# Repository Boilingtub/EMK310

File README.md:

#========== Implemented Mappings Final ===========
RA0 - SSD-0
RA1 - SSD-1
RA2 - SSD-2
RA3 - SSD-3
RA4 - SSD-4
RA5 - SSD-5
RA6 - SSD-6
RA7 - 

RB0 - USB-to-UART RST
RB1 - 
RB2 - 
RB3 - MOTOR_2_B
RB4 - 
RB5 - Capacitive Touch Sensor
RB6 -  
RB7 - LEDB

RC0 - LEDR
RC1 - LEDG
RC2 - (CCP1) MOTOR_1_B 
RC3 - SCL 1
RC4 - SDA 1
RC5 - Sensor 2
RC6 - Sensor 1
RC7 - Sensor 0

RD0 - SCL2
RD1 - SDA2
RD2 - Sensor 5
RD3 - Sensor 4
RD4 - 
RD5 - 
RD6 - TX
RD7 - RX

RE0 - MOTOR_2_F 
RE1 - 
RE2 - MOTOR_1_F
RE3 - PROGRAMMING PIN

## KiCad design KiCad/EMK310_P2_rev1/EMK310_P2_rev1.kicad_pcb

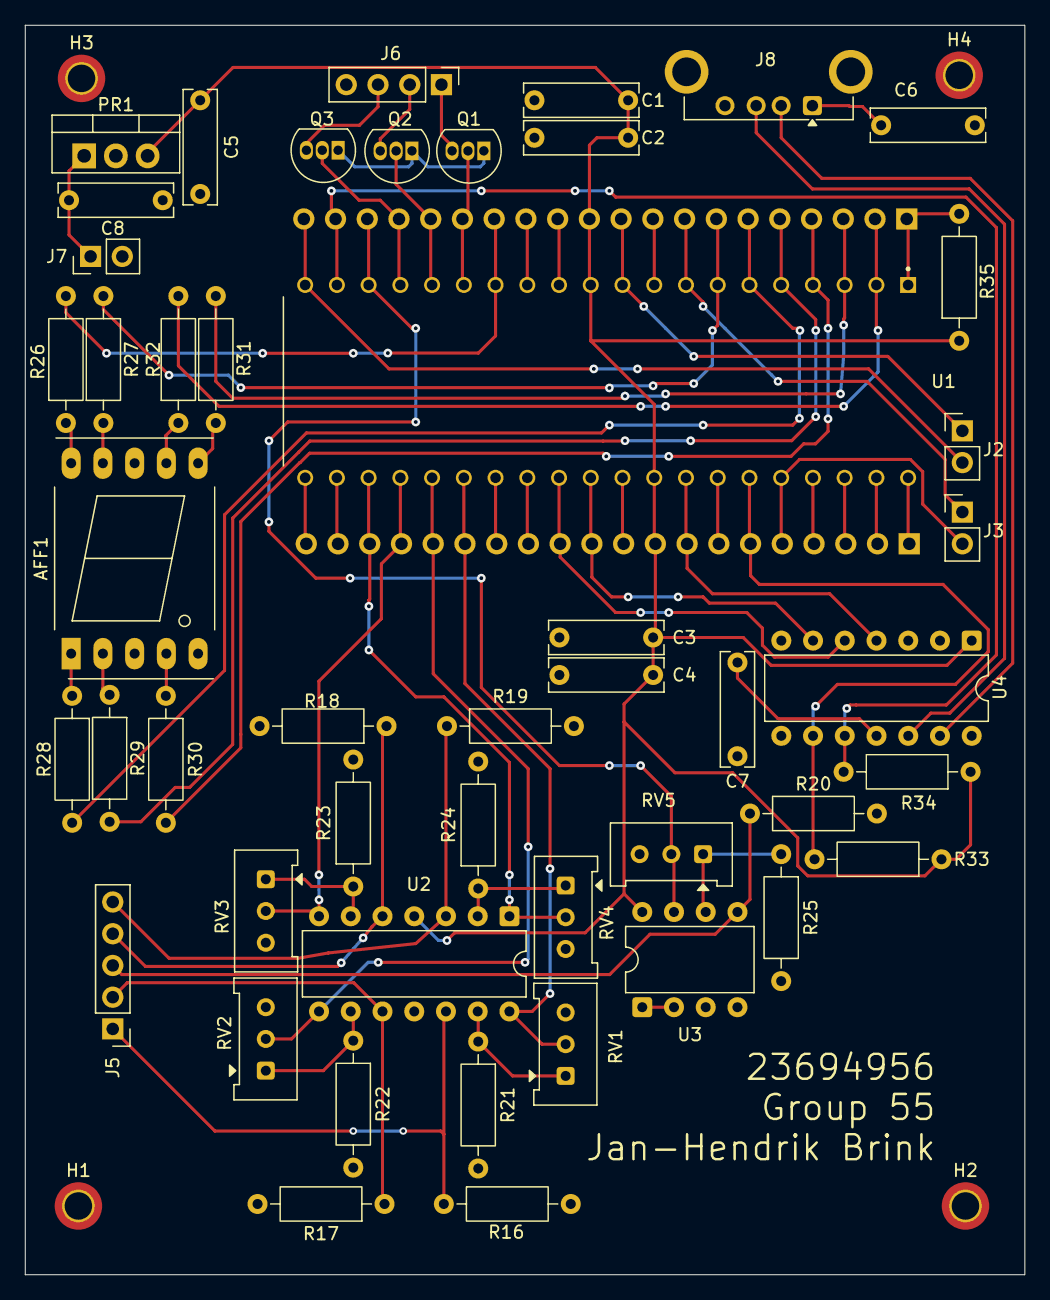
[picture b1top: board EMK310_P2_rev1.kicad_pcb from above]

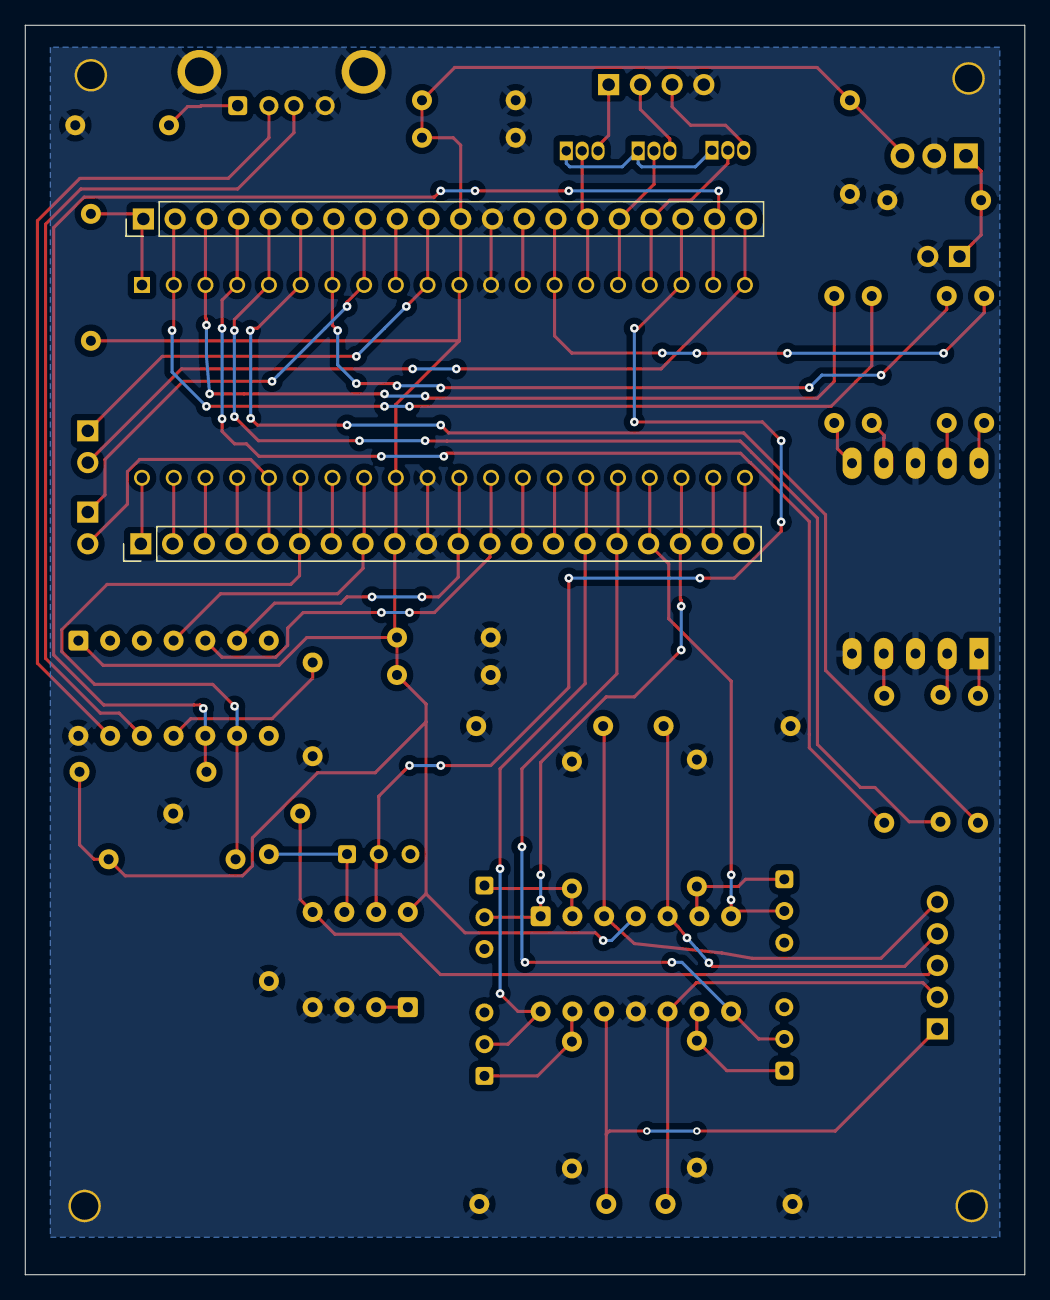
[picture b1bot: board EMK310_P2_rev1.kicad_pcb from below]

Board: 2 copper layers, 80.0 x 100.0 mm, 54 parts (2 on the bottom side), 64 nets.

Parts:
AFF1: LTS-6980HR; 7SegmentLED_LTS6760_LTS6780
C1, C2, C3, C4: C_Small; C_Rect_L9.0mm_W2.5mm_P7.50mm_MKT
C5: 10uF; C_Rect_L9.0mm_W2.5mm_P7.50mm_MKT
C6, C7, C8: 0.22uF; C_Rect_L9.0mm_W2.5mm_P7.50mm_MKT
H1, H2, H3, H4: MountingHole_Pad; MountingHole_2.2mm_M2_DIN965_Pad_TopOnly
J1, J4: Conn_01x20_Socket; PinHeader_1x20_P2.54mm_Vertical
J2, J3, J7: Conn_01x02_Socket; PinHeader_1x02_P2.54mm_Vertical
J5: Conn_01x05_Socket; PinHeader_1x05_P2.54mm_Vertical
J6: Conn_01x04_Socket; PinHeader_1x04_P2.54mm_Vertical
J8: USB_A; USB_A_Connfly_DS1095
PR1: TO-220-3_Vertical
Q1, Q2, Q3: VP0610L; TO-92L_Inline
R16, R17, R18, R19, R20, R21, R22, R23, R24, R25, R26, R27, R28, R29, R30, R31, R32: R; R_Axial_DIN0207_L6.3mm_D2.5mm_P10.16mm_Horizontal
R33, R34, R35: 10k; R_Axial_DIN0207_L6.3mm_D2.5mm_P10.16mm_Horizontal
RV1, RV2, RV3, RV4, RV5: R_Potentiometer; Potentiometer_Bourns_3386W_Horizontal
U1: PIC18F45K22; DIP1543W47P254L5321H635Q40
U2: Opamp_Quad; DIP-14_W7.62mm
U3: Opamp_Dual; DIP-8_W7.62mm
U4: MCP2221AxP; DIP-14_W7.62mm

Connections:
+9V: C8.2, J7.1, PR1.1 (Vi)
/Calib: J1.4, U1.37 (RB4)
/CapTouch: J1.3, U1.38 (RB5)
/LEDB: J4.17, Q3.2 (G), U1.17 (RC2)
/LEDG: J4.16, Q2.2 (G), U1.16 (RC1)
/LEDR: J4.15, Q1.2 (G), U1.15 (RC0)
/MOTOR_1_B: J2.2, J4.20, U1.20 (RD1)
/MOTOR_1_F: J2.1, J4.10, U1.10 (RE2)
/MOTOR_2_B: J1.5, J3.2, U1.36 (RB3)
/MOTOR_2_F: J3.1, J4.8, U1.8 (RE0)
/SCL: J4.19, R34.2, U1.19 (RD0), U4.10 (SCL)
/SDA: J1.6, R33.2, U1.35 (RB2), U4.9 (SDA)
/Vdd: C1.1, C2.1, C3.1, C4.1, C5.2, J1.9, J4.11, PR1.3 (Vo), Q1.1 (S), Q2.1 (S), Q3.1 (S), R33.1, R34.1, R35.1, U1.11 (VDD), U1.32 (VDD), U2.4 (V+), U3.8 (V+), U4.1 (VDD)
GNDREF: AFF1.3 (C.K.), AFF1.5 (DP), AFF1.8 (C.K.), C1.2, C2.2, C3.2, C4.2, C5.1, C6.2, C7.2, C8.1, H1.1, H2.1, H3.1, H4.1, J1.10, J4.12, J6.4, J7.2, J8.4 (GND), J8.5 (Shield), PR1.2 (GND), R16.2, R17.2, R18.2, R19.2, R20.2, R21.2, R22.2, R23.2, R24.2, R25.2, U1.12 (VSS), U1.31 (VSS), U2.11 (V-), U3.3 (+), U3.4 (V-), U4.14 (VSS)
unnamed: AFF1.7 (a), R32.1
unnamed: AFF1.6 (b), R31.1
unnamed: AFF1.4 (c), R30.1
unnamed: AFF1.2 (d), R29.1
unnamed: AFF1.1 (e), R28.1
unnamed: AFF1.9 (f), R27.1
unnamed: AFF1.10 (g), R26.1
unnamed: J5.1, R16.1, U2.12 (+)
unnamed: J5.2, R17.1, U2.10 (+)
unnamed: J5.4, R18.1, U2.5 (+)
unnamed: J5.5, R19.1, U2.3 (+)
unnamed: J5.3, R20.1, U3.5 (+)
unnamed: J1.1, U1.40 (RB7/PGD)
unnamed: J1.2, U1.39 (RB6/PGC)
unnamed: J1.7, U1.34 (RB1)
unnamed: J1.8, U1.33 (RB0), U4.4 (~RST)
unnamed: J1.11, U1.30 (RD7), U4.6 (UTx)
unnamed: J1.12, U1.29 (RD6), U4.5 (URx)
unnamed: J1.13, U1.28 (RD5)
unnamed: J1.14, U1.27 (RD4)
unnamed: J1.15, RV1.2, U1.26 (RC7), U2.14
unnamed: J1.16, RV2.2, U1.25 (RC6), U2.8
unnamed: J1.17, RV3.2, U1.24 (RC5), U2.7
unnamed: J1.18, RV4.2, U1.23 (RC4), U2.1
unnamed: J1.19, U1.22 (RD3)
unnamed: J1.20, U1.21 (RD2)
unnamed: J4.1, R35.2, U1.1 (RE3/Vp)
unnamed: J4.2, R32.2, U1.2 (RA0)
unnamed: J4.3, R31.2, U1.3 (RA1)
unnamed: J4.4, R30.2, U1.4 (RA2)
unnamed: J4.5, R29.2, U1.5 (RA3)
unnamed: J4.6, R28.2, U1.6 (RA4)
unnamed: J4.7, R27.2, U1.7 (RA5)
unnamed: J4.9, U1.9 (RE1)
unnamed: J4.13, U1.13 (RA7/OSC1)
unnamed: J4.14, R26.2, U1.14 (RA6/OSC2)
unnamed: J4.18, RV5.2, U1.18 (RC3), U3.7
unnamed: J6.1, Q1.3 (D)
unnamed: J6.2, Q2.3 (D)
unnamed: J6.3, Q3.3 (D)
unnamed: J8.3 (D+), U4.12 (D-)
unnamed: J8.2 (D-), U4.13 (D+)
unnamed: C6.1, J8.1 (VBUS)
unnamed: R24.1, RV4.1, U2.2 (-)
unnamed: R23.1, RV3.1, U2.6 (-)
unnamed: R22.1, RV2.1, U2.9 (-)
unnamed: R21.1, RV1.1, U2.13 (-)
unnamed: U3.1, U3.2 (-)
unnamed: R25.1, RV5.1, U3.6 (-)
unnamed: C7.1, U4.11 (VUSB)

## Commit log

2026-02-17 renamed file
2026-02-22 Add files via upload
    Calibrate code part 1
2026-02-24 added file layout
2026-02-24 added macros include file
2026-02-25 Re-organised file structure to stop redundant compilation
2026-02-25 added primary code
2026-02-25 Added Readme and modified setup
2026-02-25 Changed port layout
2026-02-25 Added lli_test and line_location-interpreter
2026-02-25 I removed some unnessasary code and added some comments
2026-02-25 Added comments and cleaned some comments out
2026-02-25 I made only the logic appearf in line_location_interpreter I also updated the lli_test to have more of the correct code to be able to test The code is not runnable yet as it needs to get integrated i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
2026-02-25 Fixed issues with code layout
2026-02-25 Added Interrupts to main branch
2026-02-26 I fixed the lli_testing to work I made button S2 work on the board by making bit 5 of portc input
2026-02-28 PWM implementation of calibration
2026-03-02 First working
2026-03-04 Started with Practical 2 codec
2026-03-05 Added Color Detection to Practical 2
2026-03-05 Added testing Values for max and min thresholds
2026-03-06 Commited file changes
2026-03-07 Working Strobing Implementation
2026-03-07 Increased ADC speed
2026-03-09 No Change
2026-03-10 added prac 2
2026-03-21 Fixed Access bank issues
2026-03-22 All working, LLI problematic
2026-03-23 Modified LLI to use ,0 for movf and improved color selection fn
2026-03-23 Fully working V1.0
2026-03-24 First integration efforts
2026-03-24 changed setup for ADCCON2
2026-04-07 Added KiCad PCB design, and updates to Practical 2
2026-04-09 50% not color detecting
2026-04-09 Updated PCB Design
2026-04-10 Added mounting Holes to PCB design
2026-04-10 Latest Not doing 2nd LLI run
2026-04-10 WOrking git statusgit status
2026-04-13 work
2026-04-13 Demo code 2026-04-13
2026-04-13 Demo code 2026-04-13 & PCB 2026-04-12 submitted to rapidM
2026-05-14 First commit, Updated Setup for new pins and seach decsicion algorithm
2026-05-14 updated Reame
2026-05-16 Updated ports to match PCB
2026-05-17 Working Serial Comms
2026-05-18 simulate and eeprom
2026-05-18 modes
2026-05-21 Race-Day code
2026-05-21 Race day code
2026-05-21 Race code minimized, NOT-debugged
2026-05-21 Race individual sensor detect
2026-05-21 Race ready
2026-05-21 Race-Ready
2026-05-22 RACE_NEW
2026-05-22 Differential Motors
2026-05-22 change slights plz
2026-05-23 RACE_READY_1
2026-05-24 raCE_EXPERIMENT
2026-06-09 new final code
